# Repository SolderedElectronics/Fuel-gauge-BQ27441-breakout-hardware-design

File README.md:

# Fuel gauge BQ27441 breakout Hardware Design

## About the Product

|  |
| :----------------------------------------------------------: |
| [Buy Fuel gauge BQ27441 breakout](https://www.solde.red/333065) |

Fuel gauge is a special type of accessory for lithium batteries that very precisely measures the state of the battery. This includes current voltage [mV], state of charge [%] and probably most interestingly: remaining capacity in the battery [mAh]. It is used with 1S batteries, and provides all this information via the I2C interface.

On our board you can find easyC connectors which allow I2C communication with microcontroller. Also, there is a JST input for any pouch battery you can find in our offer, as well as quick connect terminal connector for input if your source doesn’t have JST connector.

---

## Repository Contents

This repository contains all design files for Fuel gauge BQ27441 breakout, organized as follows:

- **`CAD` folder**: Contains KiCAD design files, including:
  - Schematics
  - PCB layout
  - Panel PCB layout
  - Source 3D files in Fusion360, if any
  - All files are sorted by version with a detailed change log.
- **`OUTPUTS` folder**: Includes all production-ready files, such as:
  - Bill of Materials (BOM) and interactive BOM (iBOM)
  - PDF versions of schematics
  - 3D `.step` file of the board
  - 3D-printable models
  - Gerber files for PCB manufacturing
  - Image of the pinout of the board
  - Product image
  - Compliance, legal and generic sales documents

Refer to the `Change Log` in the CAD folder for details about updates between versions.

---

## Learn More About the Product

Beyond the repository, explore the following resources:

### Soldered Verify

The **Soldered Verify** system ensures every board you purchase from Soldered is fully functional. It also provides access to exclusive test data for your product. To get started, find the unique Soldered Verify ID on your product's packaging and enter the ID on the [Soldered Verify page](https://soldered.com/verify/) to access test results and additional product details.

### Soldered Community

Soldered Community is your go-to place for technical support. Our engineers track and answer all questions posted there, and it’s a great space for the maker community. Get answers to your questions and solutions for your challenges at [Soldered Community](https://soldered.com/community).

### solde.red

solde.red is an ultimate URL shortener and information hub. Access it by typing solde.red/ followed by your product SKU, e.g., [solde.red/333000](https://solde.red/333000), to find getting-started guides, datasheets, open-source hardware and software files, certifications, images, pinouts, and more. Read more about the shortener [here](https://solde.red/info/).

---

## Contributing

Contributions are welcome! Here’s how you can get involved:

- Submit pull requests to enhance the design or fix issues.
- Report bugs or problems by opening an issue.

We encourage community collaboration to make this product even better.

---

## About Soldered

[Soldered for Makers](https://soldered.com) specializes in designing and manufacturing electronic products tailored for enthusiasts, ranging from hobbyists to professionals. Our portfolio includes electronic boards, sensors, and actuators that are widely utilized in fields such as microelectronics, mechatronics, robotics, programming, and IoT. Every product we offer is designed in-house and built upon open-source hardware and software platforms. Proudly certified and manufactured within the European Union, our catalog likely includes the product you need for your project.

We complement these products with comprehensive tutorials and manuals, product descriptions, schematics, programming codes, and project examples. Our round-the-clock [customer and technical support](https://soldered.com/community) is available for all our products, irrespective of the sales channel. Soldered’s success and services reflect our maker community’s unwavering [trust](https://www.trustpilot.com/review/soldered.com), for which we are deeply grateful. Join our community and create using Soldered products.

---

## License

All Soldered open-source hardware (OSH) is under The TAPR Open Hardware License. Read more in the LICENSE file located in this repository.

**Disclaimer:**

No warranty - all designs in this repository are distributed in the hope that they will be useful, but without any warranty. They are provided "AS IS", therefore without warranty of any kind, either expressed or implied. The entire quality and performance of what you do with the contents of this repository are your responsibility. In no event Soldered Electronics will be liable for your damages, or losses, including any general, special, incidental, or consequential damage arising out of the use or inability to use the contents of this repository. 

---

## Have fun!

Thank you for your support from your fellow makers at Soldered Electronics.

Happy Making!

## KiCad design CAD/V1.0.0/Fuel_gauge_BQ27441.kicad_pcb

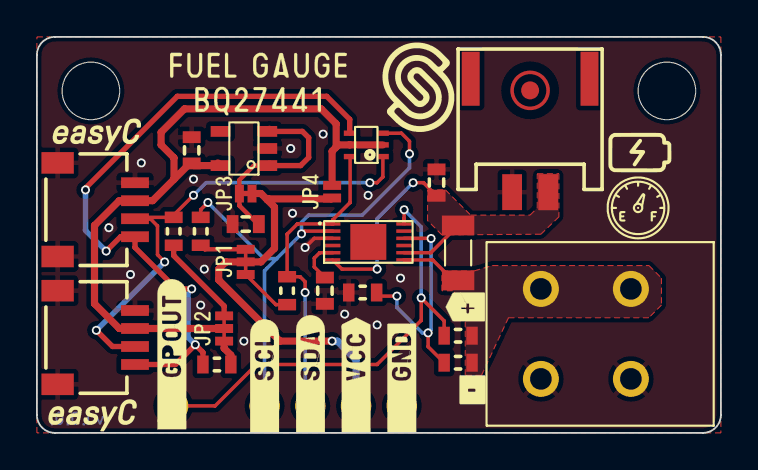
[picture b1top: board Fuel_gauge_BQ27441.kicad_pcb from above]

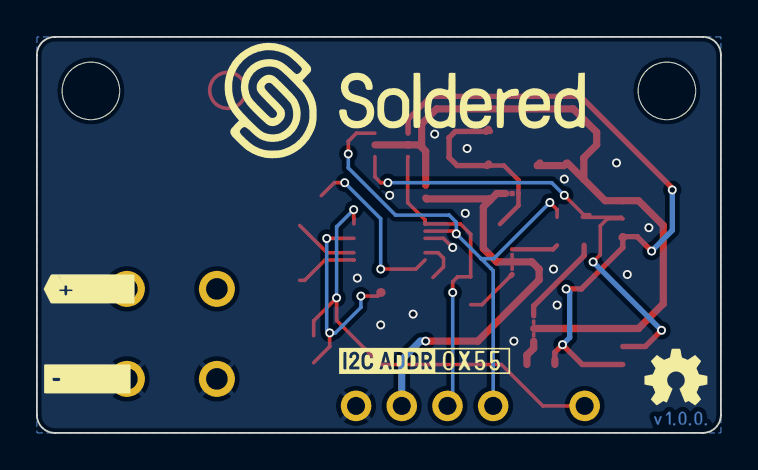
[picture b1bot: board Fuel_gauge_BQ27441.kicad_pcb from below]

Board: 2 copper layers, 38.0 x 22.0 mm, 30 parts (3 on the bottom side), 17 nets.

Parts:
C1, C2: 1u; 0603C
C3, C4: 2.2uF; 0603C
FD1: FIDUCIAL; FIDUCIAL_23
Ge: LOGO; Logo-Front-easyC-5mm
H1, H2: HOLE_3.2mm
JP1, JP2: SMD_JUMPER_3_PAD_TRACE
JP3: SMD-JUMPER-CONNECTED_TRACE_SLODERMASK
JP4: SMD_JUMPER
K1: HEADER_MALE_1X1
K2: JST-2pin-SMD
K3: TERMINAL_KF235-5.0-2P
K4, K5: easyC-SMD; easyC-connector
K6: HEADER_MALE_4X1
R1, R2, R3, R4: 10k; 0603R
R5, R8: 10K; 0603R
R6: 0.010R; 1206R
R7: 1.8M; 0603R
Ref**: Val**; Version1.0.0.
U1: BQ27441
U2: NMOS-DUAL; SOT-363
U3: SE5218; SOT-23-5

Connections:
3V3: C4.2, JP2.2, JP4.2, K4.3 (3V3), K5.3 (3V3), U2.2 (G2), U2.5 (G1), U3.5 (VOUT)
5V: JP1.2, JP3.2, JP4.1, K6.2
BIN: R5.2, R7.1, U1.10 (BIN)
GND: C1.1, C2.1, C3.1, C4.1, K2.2 (-), K3.2, K4.4 (GND), K4.5 (SHIELD), K5.4 (GND), K5.5 (SHIELD), K6.1, R5.1, U1.3 (VSS), U3.2 (GND)
GPOUT: K1.1, R8.1, U1.12 (GPOUT)
unnamed: C1.2, U1.5 (VDD)
unnamed: C3.2, JP3.1, U3.1 (VIN), U3.3 (EN)
SCL3,3: K4.1 (SCL), K5.1 (SCL), R4.1, U2.4 (S1)
SCL5: K6.4, R2.2, U1.2 (SCL), U2.3 (D1)
SCL_PULL3,3: JP2.1, R4.2
SCL_PULL5: JP1.1, R2.1
SDA3,3: K4.2 (SDA), K5.2 (SDA), R1.2, U2.1 (S2)
SDA5: K6.3, R3.1, U1.1 (SDA), U2.6 (D2)
SDA_PULL3,3: JP2.3, R1.1
SDA_PULL5: JP1.3, R3.2
VCC: C2.2, K2.1 (+), R6.1, U1.6 (BAT), U1.8 (SRP)
VSYS: K3.1, R6.2, R7.2, R8.2, U1.7 (SRN)

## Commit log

2022-08-06 Updating open source files.
